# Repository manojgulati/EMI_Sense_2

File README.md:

EMI_Sense_2
===========

Revisiting EMI Sensing for Appliance Disaggregation

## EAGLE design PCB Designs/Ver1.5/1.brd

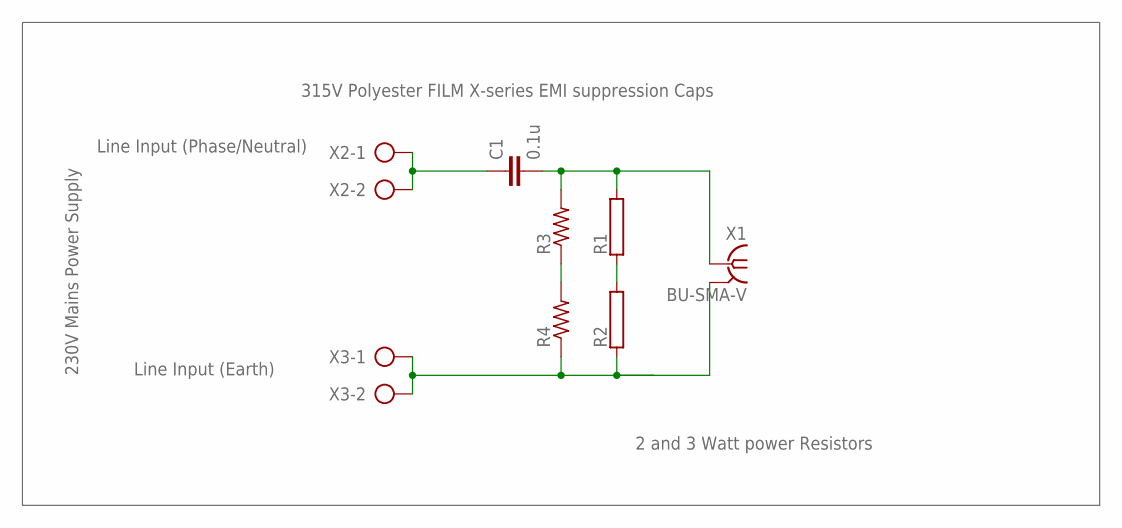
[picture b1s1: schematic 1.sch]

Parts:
C1: 0.1u; C15B5
R1, R2: RAC01; AC01
R3, R4: R-US_M1206; M1206
X1: BU-SMA-V
X2, X3: AK500/2

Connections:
GND: X1.3 (GND), X1.4 (GND), X1.5 (GND)
unnamed: R3.1, R4.2
unnamed: R1.1, R2.2
unnamed: C1.2, R1.2, R3.2, X1.1
unnamed: C1.1, X2.1, X2.2
unnamed: R2.1, R4.1, X1.2 (GND), X3.1, X3.2

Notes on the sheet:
Line Input (Phase/Neutral)
Line Input (Earth)
230V Mains Power Supply
2 and 3 Watt power Resistors
315V Polyester FILM X-series EMI suppression Caps

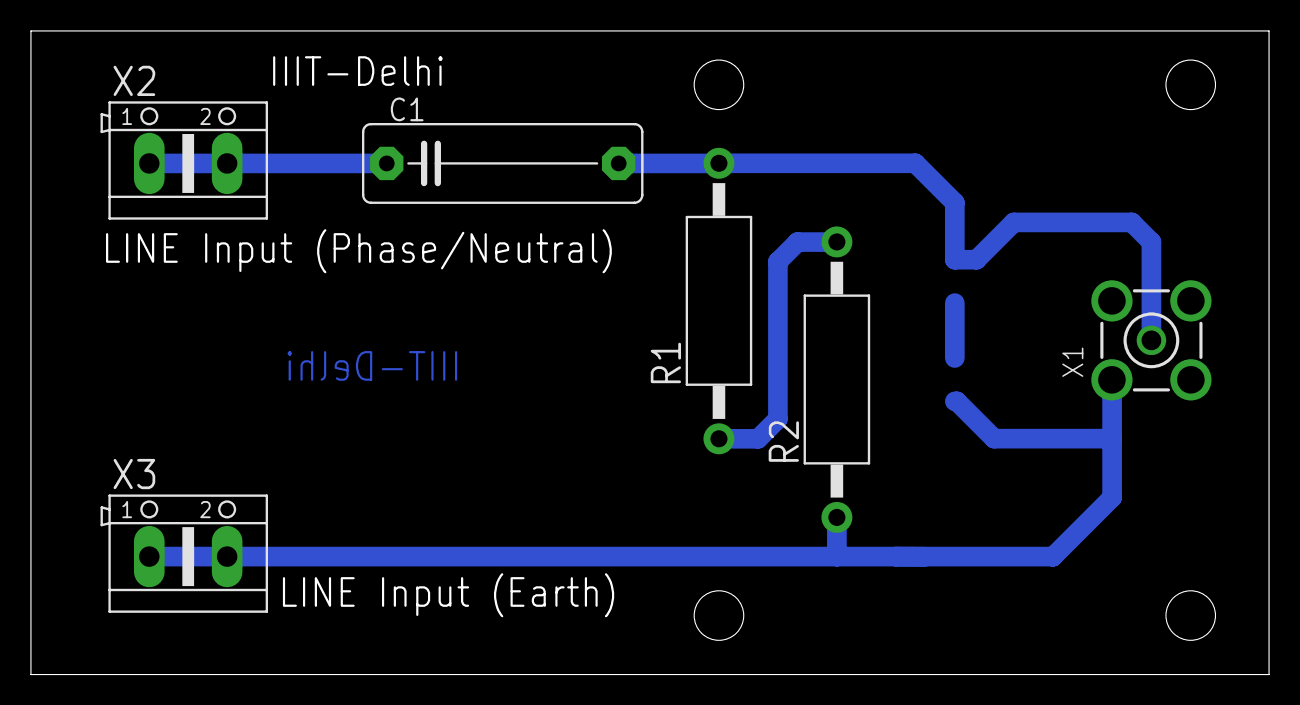
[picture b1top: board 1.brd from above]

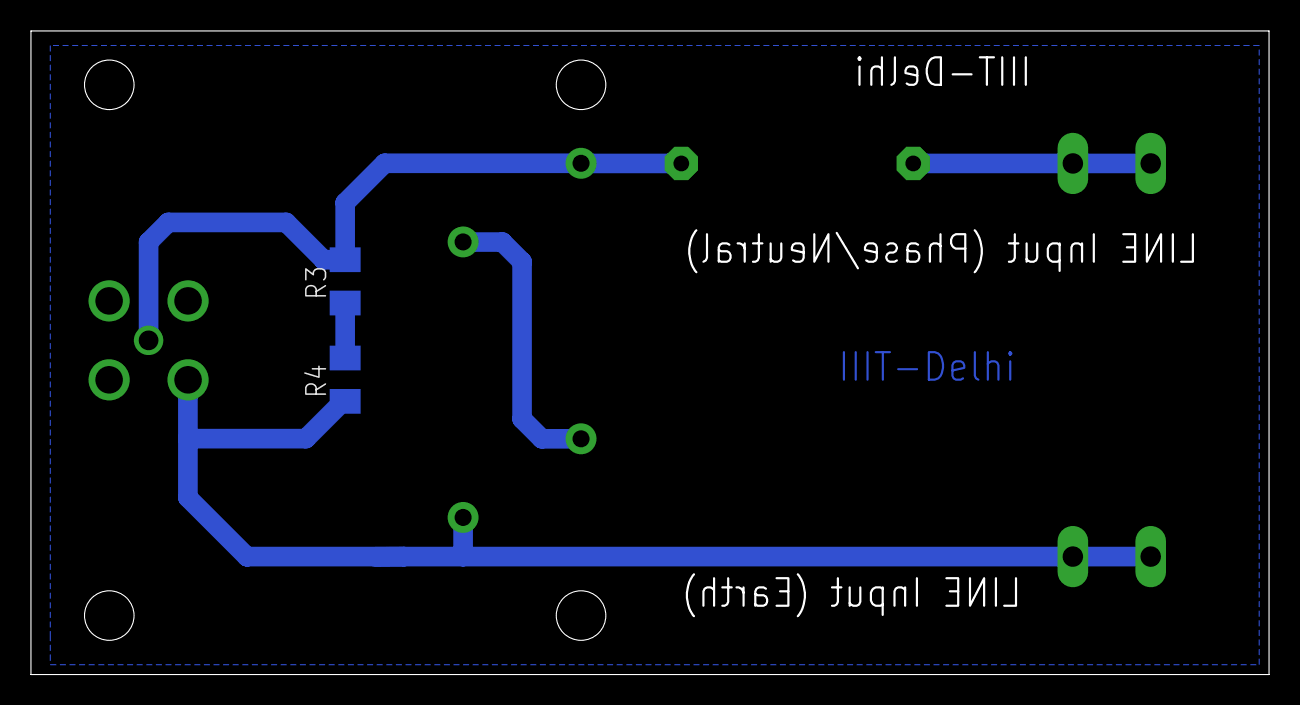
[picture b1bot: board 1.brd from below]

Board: 2 copper layers, 80.0 x 41.6 mm, 8 parts (2 on the bottom side), 6 nets.

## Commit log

2014-11-24 Spice Model for CM DM Flow Analysis
2014-12-09 Update Simulation files, PCB design filters
2014-12-09 Small change
2014-12-10 Updated Scripts for CM and DM computation
    Added a function to plot4publication along with an improved script for
    CM and DM computation
2014-12-12 Updated script for FFT computation removed bug for ADC conversion
2014-12-15 Updated Script for computing FFT
2014-12-16 Updated script
2014-12-17 added inset script
2014-12-18 updated script to plot in semilogx scale
2014-12-21 Unknown Update
2014-12-23 Updated scripts
    Rectified bug in matlab script and added spice models for 3-phase
    simulations
2014-12-26 Added scripts
2014-12-30 added spice models for earth current measurements
2015-01-06 Added Script
